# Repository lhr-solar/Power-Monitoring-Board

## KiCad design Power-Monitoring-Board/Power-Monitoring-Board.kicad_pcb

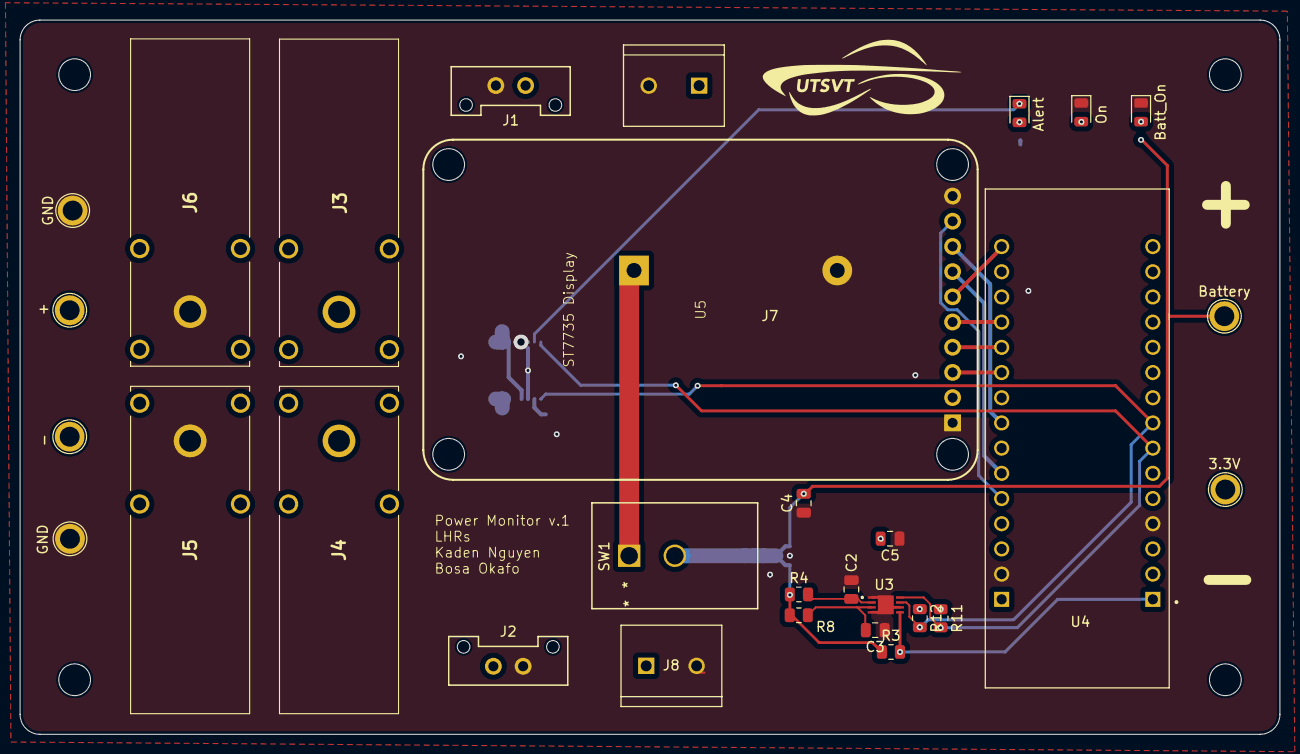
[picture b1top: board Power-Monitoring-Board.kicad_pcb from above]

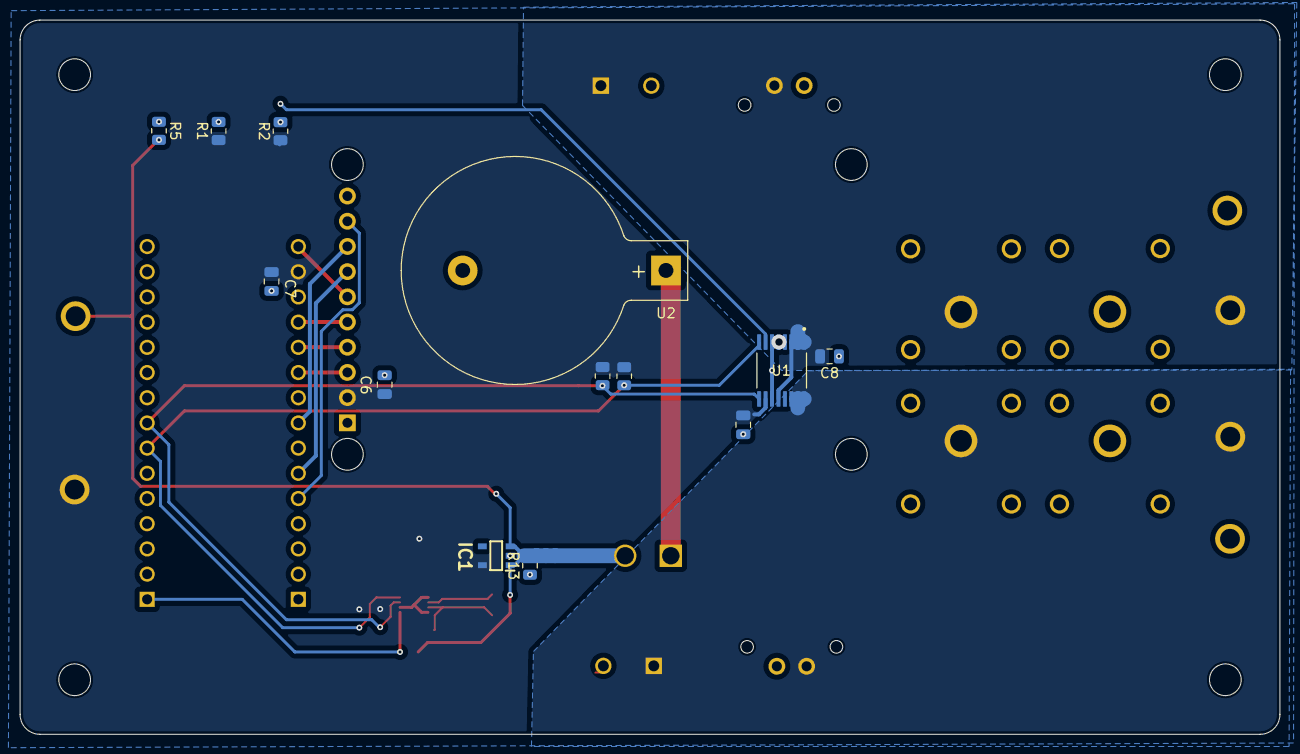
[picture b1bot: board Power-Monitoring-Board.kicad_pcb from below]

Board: 2 copper layers, 127.0 x 72.0 mm, 43 parts (13 on the bottom side), 22 nets.

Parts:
3.3V: TestPoint; TestPoint_Plated_Hole_D2.0mm
-: TestPoint; TestPoint_Plated_Hole_D2.0mm
Alert: Alert_LED; LED_0805_2012Metric
Batt_On: Batt_On_LED; LED_0805_2012Metric
Battery: TestPoint; TestPoint_Plated_Hole_D2.0mm
C1, C8: 0.1uF; C_0805_2012Metric
C2, C4: 1uF; C_0805_2012Metric
C3: 10nF; C_0805_2012Metric
C5: 2.2uF; C_0805_2012Metric
C6, C7: 1u; C_0805_2012Metric
GND: TestPoint; TestPoint_Plated_Hole_D2.0mm
GND#2: TestPoint; TestPoint_Plated_Hole_D2.0mm
IC1: XC6222D331MR-G; SOT95P280X130-5N
J1, J2: Conn_01x02_Pin; Molex_MicroFit3.0_1x2xP3.00mm_PolarizingPeg_Vertical
J3, J4, J5, J6: Conn_01x01_Pin; Banana_Jack_Horizontal
J7, J8: Conn_01x02_Pin; screw_termina2x1
On: On_LED; LED_0805_2012Metric
R1, R2, R5, R9, R10, R11, R12, R13: 10k; R_0805_2012Metric
R3: 4.7k; R_0805_2012Metric
R4: 1K; R_0805_2012Metric
R8: 150; R_0805_2012Metric
SW1: GF-123-0054; SW2_GF-123-0054_CWI
TP1: TestPoint; TestPoint_Plated_Hole_D2.0mm
U1: INA260AIPWR; INA260
U2: CR2450; BatteryHolder_Keystone_103_1x20mm
U3: MAX17043G+U; 21-0174B_MXM
U4: NUCLEO_L432KC; MODULE_NUCLEO-L432KC
U5: ST7735R; ST7735

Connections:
+3.3V: 3.3V.1, C1.1, C5.2, C6.1, C7.1, IC1.5 (VOUT), R1.1, R2.1, R9.1, R10.2, R11.1, R12.1, U1.10 (VS), U4.CN4_14 (+3V3), U5.2 (VCC)
/ALERT: R3.2, U3.5 (*ALRT), U4.CN3_1 (PA9)
/Batt: Battery.1, C4.2, IC1.1 (VIN), IC1.3 (CE), R3.1, R4.1, R5.2, R8.1, R13.2, SW1.2
/CARD_CS: U4.CN4_12 (PA0), U5.5 (CARD_CS)
/DC: U4.CN4_11 (PA1), U5.4 (DC)
/MISO: U4.CN4_5 (PA2), U5.9 (MISO)
/MOSI: U4.CN4_6 (PA7), U5.7 (MOSI)
/RESET: U4.CN4_10 (PA3), U5.3 (Reset)
/SCK: U4.CN4_8 (PA5), U5.8 (SCK)
/SCL: R10.1, R12.2, U1.9 (SCL), U3.7 (SCL), U4.CN3_8 (PB6)
/SDA: R9.2, R11.2, U1.8 (SDA), U3.8 (SDA), U4.CN3_7 (PB7)
/TFT_CS: U4.CN4_15 (PB3), U5.6 (TFT_CS)
/V+: C8.2, J1.1, J3.1, J7.1, TP1.1, U1.1 (IN+), U1.2 (IN+), U1.3 (IN+), U1.12 (VBUS)
/V-: -.1, J2.1, J4.1, J8.1, U1.14 (IN-), U1.15 (IN-), U1.16 (IN-)
GND: Batt_On.1 (K), C1.2, C2.1, C3.1, C4.1, C5.1, C6.2, C7.2, C8.1, GND.1, GND#2.1, IC1.2 (VSS), J1.2, J2.2, J5.1, J6.1, J7.2, J8.2, On.1 (K), R13.1, U1.4 (A1), U1.5 (A0), U1.6 (GND), U1.11 (GND), U2.2 (-), U3.1 (CTG), U3.4 (GND), U3.6 (QSTRT), U3.9 (EPAD), U4.CN3_4 (GND), U4.CN4_2 (GND), U5.1 (GND), U5.10 (LITE)
unnamed: On.2 (A), R1.2
unnamed: Alert.2 (A), R2.2
unnamed: Alert.1 (K), U1.7 (ALERT)
unnamed: Batt_On.2 (A), R5.1
unnamed: SW1.1, U2.1 (+)
unnamed: C2.2, R4.2, U3.2 (CELL)
unnamed: C3.2, R8.2, U3.3 (VDD)

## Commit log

2024-11-09 added the power montioring board
2024-12-07 sch update
2024-12-07 update sch and footprints
2025-01-19 the newst version of the board with all the stuff
2025-02-18 layout changes
2025-02-18 more changes
2025-02-18 added labels
2025-02-18 added utsvt logo
